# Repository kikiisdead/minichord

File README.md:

# MINICHORD
 a mini omnichord made using Teensy 4.1 and the Teensy Audio Library for Digital Electronics at NYU Steinhardt Music Tech

 [YouTube Video](https://www.youtube.com/watch?v=LYFFMY3H_Zw)

# HARDWARE
 - Teensy 4.1 (could probably use a cheaper version but I have not tested it)
 - Teensy Audio Adaptor Rev D for Teensy 4.x
 - Adafruit CAP1188 
 - 7 MX compatible key switches (or equivalent, I used some Adafruit ones)
 - Adafruit SSD1306 (you may need to change the device ID macro in src/display/display.h)
 - Alps EC12E Vertical Rotary Encoder

[Mouser Project Page](https://www.mouser.com/ProjectManager/ProjectDetail.aspx?AccessID=75f0d25f79)

Does not include header pins, standoffs, or the cost to print the PCB. 

# TODO
 - Optimize the project with audio memory usage max

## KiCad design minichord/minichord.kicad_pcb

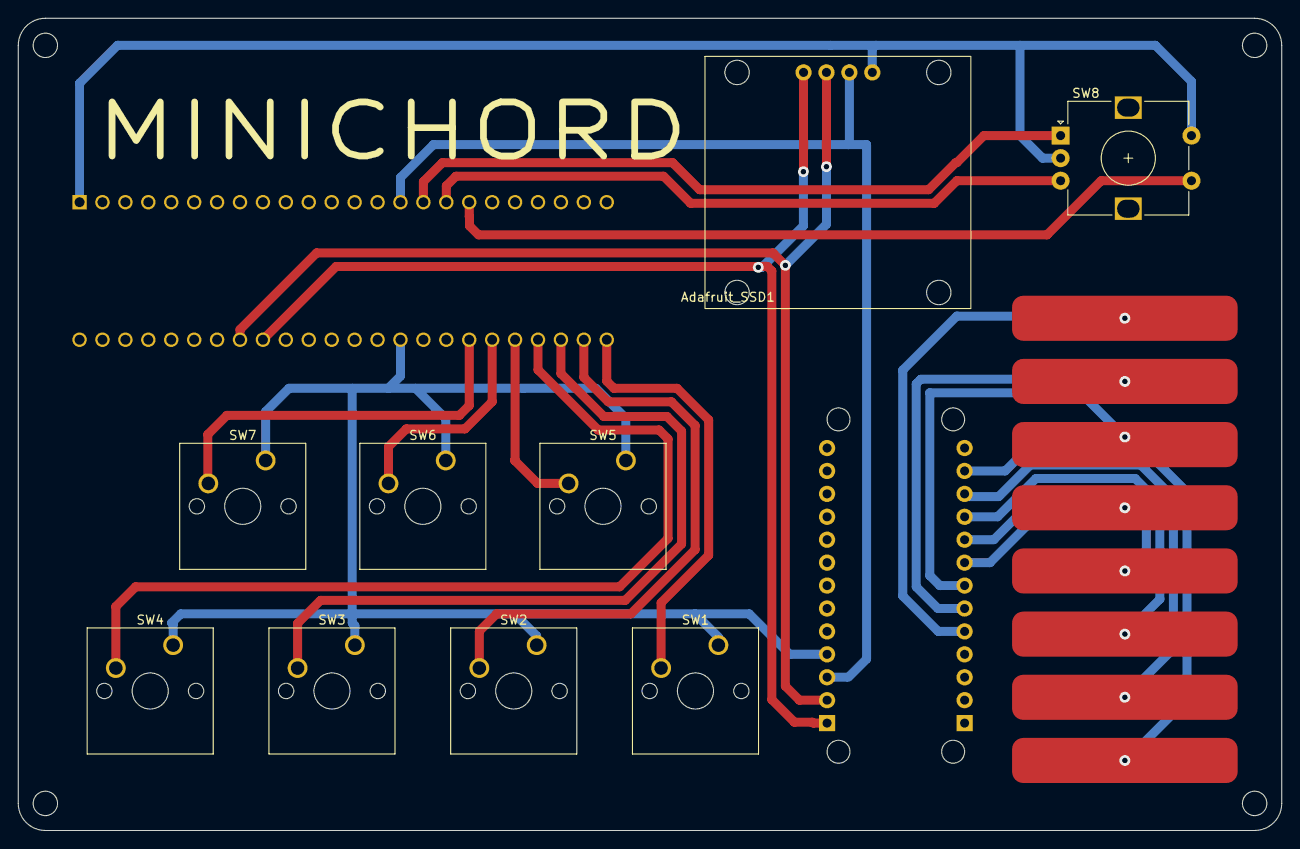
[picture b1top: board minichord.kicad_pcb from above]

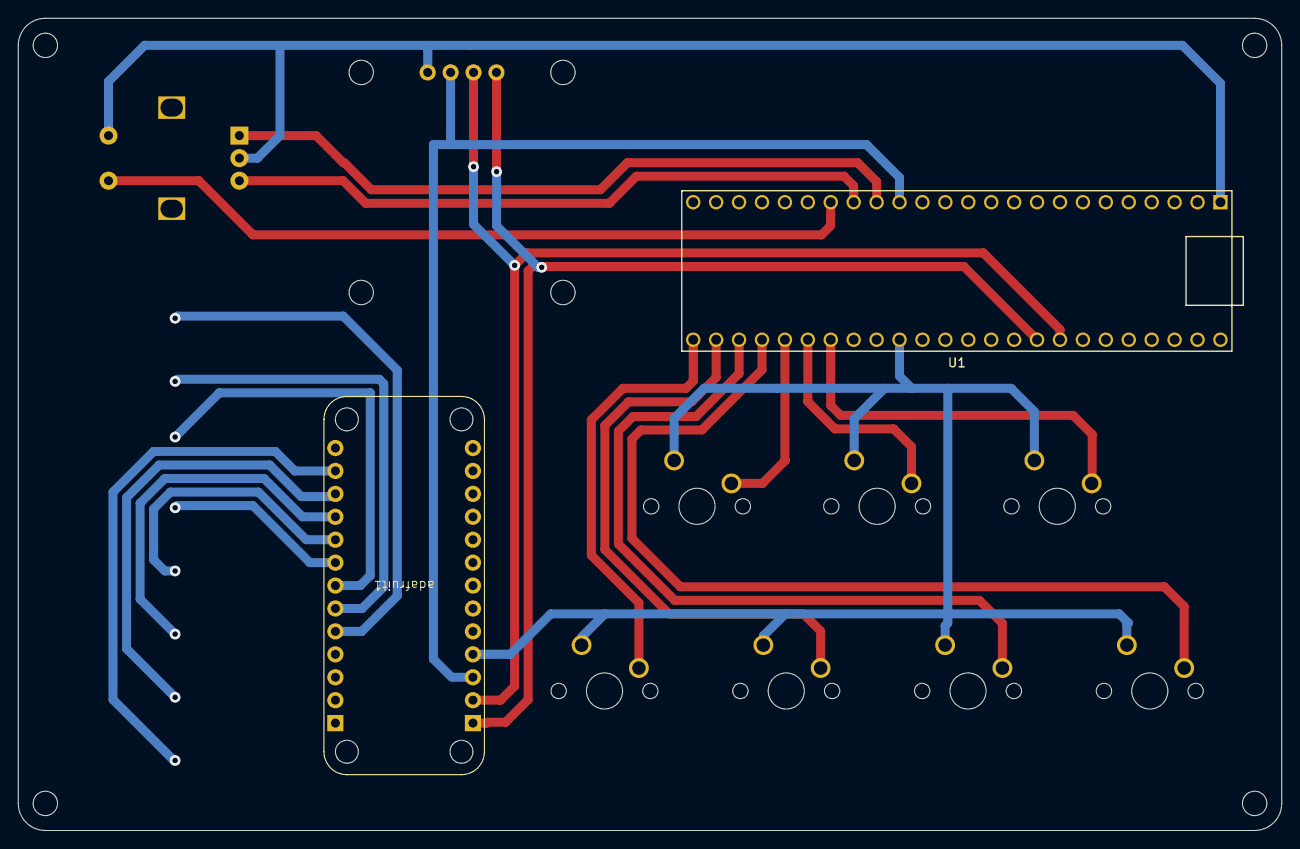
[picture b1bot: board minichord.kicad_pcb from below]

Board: 2 copper layers, 140.0 x 90.0 mm, 16 parts (2 on the bottom side), 22 nets.

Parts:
8exposedTrack1: 8touchCapacitiveTouch
Adafruit_SSD1: OLED_From_Amazon
H1, H2, H3, H4: MountingHole; MountingHole_2.7mm_M2.5
SW1, SW2, SW3, SW4, SW5, SW6, SW7: SW_Push; SW_Cherry_MX_1.00u_PCB
SW8: RotaryEncoder_Switch; RotaryEncoder_Alps_EC12E-Switch_Vertical_H20mm
U1: Teensy4.1Better; Teensy41Better
adafruit1: CAP1188; CAP1188 BREAKOUT

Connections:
+3.3V: Adafruit_SSD1.2 (VCC), U1.15 (3V3), U1.46 (3V3), adafruit1.3 (VIN)
BUTTON1: SW1.2, U1.25 (33_MCLK2)
BUTTON2: SW2.2, U1.26 (34_RX8)
BUTTON3: SW3.2, U1.27 (35_TX8)
BUTTON4: SW4.2, U1.28 (36_CS)
BUTTON5: SW5.2, U1.29 (37_CS)
BUTTON6: SW6.2, U1.30 (38_A14_CS1_IN1)
BUTTON7: SW7.2, U1.31 (39_A15_MISO1_OUT1A)
ENCODER1: SW8.A, U1.16 (24_A10_TX6_SCL2)
ENCODER2: SW8.B, U1.17 (25_A11_RX6_SDA2)
ENCODERBUTTON: SW8.S2, U1.18 (26_A12_MOSI1)
GND: Adafruit_SSD1.1 (GND), SW1.1, SW2.1, SW3.1, SW4.1, SW5.1, SW6.1, SW7.1, SW8.C, SW8.S1, U1.1 (GND), U1.34 (GND), adafruit1.4 (GND)
SCL: Adafruit_SSD1.3 (SCL), U1.41 (19_A5_SCL), adafruit1.2 (SCK)
SDA: Adafruit_SSD1.4 (SDA), U1.40 (18_A4_SDA), adafruit1.1 (SDA/MISO)
TRACK1: 8exposedTrack1.1 (PIN1), adafruit1.18 (C1)
TRACK2: 8exposedTrack1.2 (PIN2), adafruit1.19 (C2)
TRACK3: 8exposedTrack1.3 (PIN3), adafruit1.20 (C3)
TRACK4: 8exposedTrack1.4 (PIN4), adafruit1.21 (C4)
TRACK5: 8exposedTrack1.5 (PIN5), adafruit1.22 (C5)
TRACK6: 8exposedTrack1.6 (PIN6), adafruit1.23 (C6)
TRACK7: 8exposedTrack1.7 (PIN7), adafruit1.24 (C7)
TRACK8: 8exposedTrack1.8 (PIN8), adafruit1.25 (C8)

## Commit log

2024-11-18 Added Interface for Encoder Editable Parameters
    Basically utilizing pointers to simplyfy my encoder increment and decrement functions
2024-11-21 Simplifying and Stremalining
2024-12-04 KiCad Files for the PCB
2024-12-04 changed name of folder in directory
2024-12-05 KiCad Footprints and symbols for CAP1188
2024-12-06 Simplifying main program
2024-12-10 debugging display
2024-12-11 fixing smal display issue
2025-03-21 Fixing Incorrect #include
2025-03-21 Small Updates
2025-04-22 Small Update: Making more verbose Serial Monitor output
2025-04-22 Fixing Cast Typing
